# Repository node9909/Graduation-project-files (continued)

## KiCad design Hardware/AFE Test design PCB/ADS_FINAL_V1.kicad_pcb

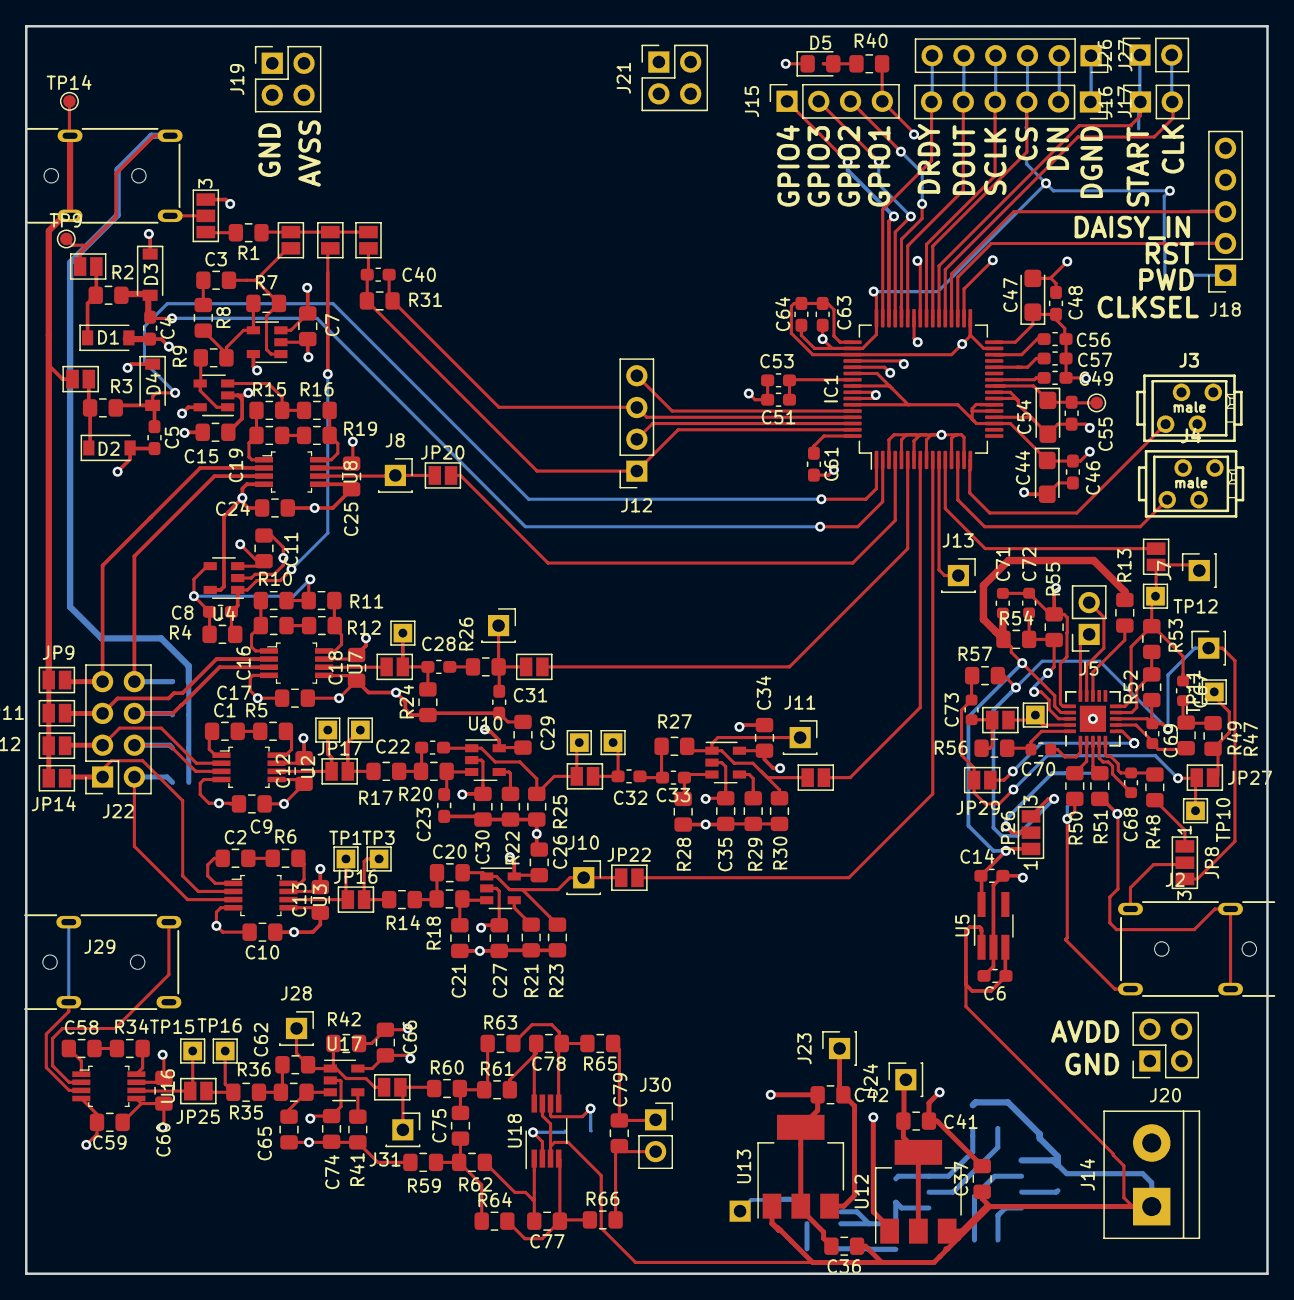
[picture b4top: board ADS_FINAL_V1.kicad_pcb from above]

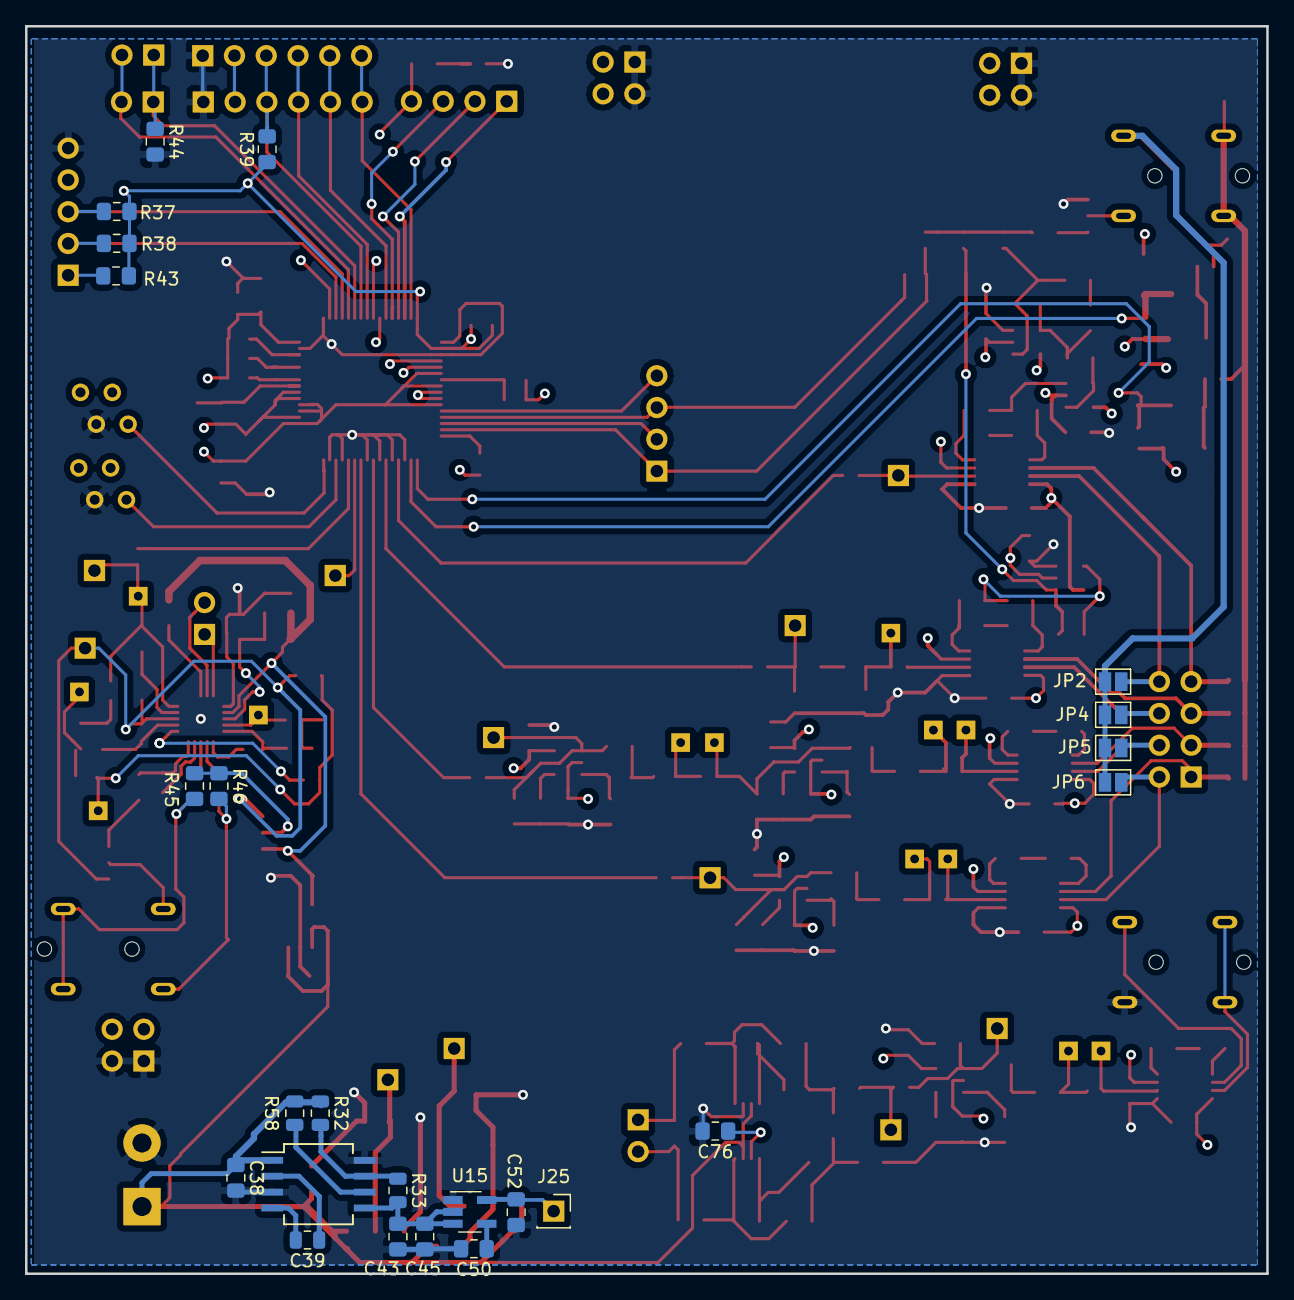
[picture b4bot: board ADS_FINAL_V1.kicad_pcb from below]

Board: 4 copper layers, 99.2 x 99.7 mm, 247 parts (24 on the bottom side), 150 nets.

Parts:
C1, C2, C16, C19, C58: 15u; C_0805_2012Metric_Pad1.15x1.40mm_HandSolder
C3: 1nF; C_0805_2012Metric_Pad1.15x1.40mm_HandSolder
C4, C5: 10pF; C_0603_1608Metric_Pad1.05x0.95mm_HandSolder
C6, C14, C49, C51, C56, C64: 1uF; C_0603_1608Metric_Pad1.05x0.95mm_HandSolder
C7, C9, C10, C11, C12, C13, C15, C17, C18, C24, C25, C26, C27, C29, C30, C34, C35, C59, C60, C66, C74, C75, C76, C77, C78, C79: 100n; C_0805_2012Metric_Pad1.15x1.40mm_HandSolder
C8: 1.5nF; C_0603_1608Metric_Pad1.05x0.95mm_HandSolder
C20, C21, C62, C65: 4.7nF; C_0805_2012Metric_Pad1.15x1.40mm_HandSolder
C22, C23: 4.7nF; C_0603_1608Metric_Pad1.05x0.95mm_HandSolder
C28, C31: 100n; C_0603_1608Metric_Pad1.05x0.95mm_HandSolder
C32, C33: 10nF; C_0603_1608Metric_Pad1.05x0.95mm_HandSolder
C36, C37, C41, C42: 1uF; C_0805_2012Metric_Pad1.15x1.40mm_HandSolder
C38, C43: 4.7uF; C_0805_2012Metric_Pad1.15x1.40mm_HandSolder
C39: 1uF; C_0805_2012Metric
C40: 1M; C_0603_1608Metric_Pad1.05x0.95mm_HandSolder
C44: 10uF; CP_EIA-3216-12_Kemet-S
C45, C52: 2.2uF; C_0805_2012Metric_Pad1.15x1.40mm_HandSolder
C46, C48, C55: 0.1u; C_0603_1608Metric_Pad1.05x0.95mm_HandSolder
C47, C54: 10uF; CP_EIA-3216-10_Kemet-I
C50: 10nF; C_0805_2012Metric_Pad1.15x1.40mm_HandSolder
C53: .1uF; C_0603_1608Metric_Pad1.05x0.95mm_HandSolder
C57: 22uF; C_0603_1608Metric_Pad1.05x0.95mm_HandSolder
C61: 1nF; C_0603_1608Metric_Pad1.05x0.95mm_HandSolder
C63: 0.1uF; C_0603_1608Metric_Pad1.05x0.95mm_HandSolder
C67, C68, C69: 1nF; C_0603_1608Metric
C70, C73: 1000nF; C_0603_1608Metric
C71, C72: 100nF; C_0603_1608Metric
D1, D2, D3, D4: D_Schottky; D_SOD-123
D5: LED; LED_0805_2012Metric_Pad1.15x1.40mm_HandSolder
IC1: ADS1298_By_Oliver; TQFP-64_10x10mm_P0.5mm
J1, J2, J29: AUDIO_JACK_By_OLIVER; MX387GL
J3, J4: external header 2; 0-215464-4_TH_4-pin_male
J5, J16, J26, J30: Conn_01x02; PinSocket_1x02_P2.54mm_Vertical
J6, J7, J8, J9, J10, J11, J13, J23, J24, J25, J28, J31: Conn_01x01; PinSocket_1x01_P2.54mm_Vertical
J12, J15: Conn_01x04; PinSocket_1x04_P2.54mm_Vertical
J14: Screw_Terminal_01x02; TerminalBlock_bornier-2_P5.08mm
J17, J27: DATA_OUT; PinSocket_1x06_P2.54mm_Vertical
J18: Conn_01x05; PinSocket_1x05_P2.54mm_Vertical
J19, J20, J21: Conn_02x02_Counter_Clockwise; PinSocket_2x02_P2.54mm_Vertical
J22: Conn_02x04_Counter_Clockwise; PinSocket_2x04_P2.54mm_Vertical
JP1, JP2, JP4, JP5, JP6, JP7, JP9, JP10, JP11, JP12, JP13, JP14, JP15, JP19: SolderJumper_2_Open; SolderJumper-2_P1.3mm_Open_Pad1.0x1.5mm
JP3, JP8: Jumper_3_Open; SolderJumper-3_P1.3mm_Open_Pad1.0x1.5mm_NumberLabels
JP16, JP17, JP18, JP20, JP21, JP22, JP23, JP24, JP25, JP30: Jumper; SolderJumper-2_P1.3mm_Open_Pad1.0x1.5mm
JP26: SolderJumper_3_Open; SolderJumper-3_P1.3mm_Open_Pad1.0x1.5mm_NumberLabels
JP27, JP28, JP29: Jumper_2_Open; SolderJumper-2_P1.3mm_Open_Pad1.0x1.5mm
M1: AD8232; LFCSP-20-1EP_4x4mm_P0.5mm_EP2.1x2.1mm
R1, R7: 100k; R_0805_2012Metric_Pad1.15x1.40mm_HandSolder
R2, R3: 5k; R_0805_2012Metric_Pad1.15x1.40mm_HandSolder
R4: 1M; R_0805_2012Metric_Pad1.15x1.40mm_HandSolder
R5, R6, R10, R11, R12, R15, R16, R19, R21, R22, R24, R26, R29, R34, R41: 1K; R_0805_2012Metric_Pad1.15x1.40mm_HandSolder
R8, R13, R37, R43, R44: 10k; R_0805_2012Metric_Pad1.15x1.40mm_HandSolder
R9, R38: 10K; R_0805_2012Metric_Pad1.15x1.40mm_HandSolder
R14, R17, R35: 36k; R_0805_2012Metric_Pad1.15x1.40mm_HandSolder
R18, R20, R36, R56, R57, R59, R60, R61, R62, R63, R64, R65, R66: 130k; R_0805_2012Metric_Pad1.15x1.40mm_HandSolder
R23, R42: 9k; R_0805_2012Metric_Pad1.15x1.40mm_HandSolder
R25: 30k; R_0805_2012Metric_Pad1.15x1.40mm_HandSolder
R27: 1.1M; R_0805_2012Metric_Pad1.15x1.40mm_HandSolder
R28: 2.2M; R_0805_2012Metric_Pad1.15x1.40mm_HandSolder
R30: 3K; R_0805_2012Metric_Pad1.15x1.40mm_HandSolder
R31: 1.5nF; R_0805_2012Metric_Pad1.15x1.40mm_HandSolder
R32: 100k; R_0805_2012Metric
R33: 50k; R_0805_2012Metric
R39: 100K; R_0805_2012Metric_Pad1.15x1.40mm_HandSolder
R40, R47, R49, R52, R53: R; R_0805_2012Metric_Pad1.15x1.40mm_HandSolder
R45, R46, R54, R55: 10M; R_0805_2012Metric_Pad1.15x1.40mm_HandSolder
R48: 390k; R_0805_2012Metric_Pad1.15x1.40mm_HandSolder
R50, R51: 180k; R_0805_2012Metric_Pad1.15x1.40mm_HandSolder
R58: 10k; R_0805_2012Metric
TP1, TP2, TP3, TP4, TP5, TP6, TP7, TP10, TP11, TP12, TP13, TP15, TP16: TestPoint; TestPoint_THTPad_1.5x1.5mm_Drill0.7mm
TP8, TP9, TP14: TestPoint; TestPoint_Pad_D1.0mm
U1, U4, U6, U9, U10, U11, U17: OPA333xxDBV; SOT-23-5
U2, U3, U7, U8, U16: INA333AIDGKR; TSSOP-8_W3mm
U5: ADP150; TSOT-23-5_HandSoldering
U12: TLV1117-25; SOT-223-3_TabPin2
U13: MCP1825S; SOT-223-3_TabPin2
U14: MAX889T; SO-8_5.3x6.2mm_P1.27mm
U15: TPS72325; SOT-23-5_HandSoldering
U18: THS4521IDGKT; VSSOP-8_3.0x3.0mm_P0.65mm

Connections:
+5V: C6.1, C36.1, C37.1, C38.1, J14.1, R32.1, R58.1, U5.1, U5.3, U12.3, U13.1, U14.1, U18.3, U18.7
/sheet794AF31F/3V_IN: C14.1, C71.2, JP26.1, M1.17, R13.2, R54.1, U5.5
/sheet794AF31F/EMG_OUT: C67.1, J7.1, JP19.1, M1.10, R53.2, TP12.1
/sheet794AF31F/SDN_MCU: M1.13, R13.1
AD-DC1: J5.2, M1.14
AVDD: C7.1, C11.1, C12.2, C13.2, C15.1, C18.2, C25.2, C26.1, C29.1, C34.1, C41.1, C44.1, C46.1, C60.2, C66.1, D3.1, D4.1, IC1.19, IC1.21, IC1.22, IC1.54, IC1.56, IC1.59, J3.1, J4.1, J20.3, J20.4, J24.1, U1.2, U2.7, U3.7, U4.2, U6.2, U7.7, U8.7, U9.5, U10.5, U11.5, U12.2, U16.7, U17.5
AVSS: C4.2, C5.2, C9.2, C10.2, C17.2, C24.2, C27.1, C30.1, C35.1, C47.1, C48.1, C49.2, C51.2, C52.1, C53.2, C54.2, C55.2, C56.2, C57.2, C59.2, C61.2, C74.1, D1.2, D2.2, IC1.20, IC1.23, IC1.24, IC1.32, IC1.53, IC1.57, IC1.58, J3.3, J4.3, J19.3, J19.4, J25.1, U1.5, U2.4, U3.4, U4.5, U6.5, U7.4, U8.4, U9.2, U10.2, U11.2, U15.5, U16.4, U17.2
CLK: IC1.37, J16.2, J26.2
CLKSEL: IC1.52, J18.1, R43.2
CS: IC1.39, J17.3, J27.3, R39.2
DAISY_CON_1: IC1.41, J18.4
DGND: C6.2, C7.2, C9.1, C10.1, C11.2, C12.1, C13.1, C14.2, C15.2, C17.1, C18.1, C21.1, C23.1, C24.1, C25.1, C26.2, C27.2, C29.2, C30.2, C31.1, C34.2, C35.2, C36.2, C37.2, C38.2, C41.2, C42.2, C43.2, C44.2, C45.2, C46.2, C47.2, C48.2, C50.2, C52.2, C59.1, C60.1, C63.2, C64.2, C65.1, C66.2, C71.1, C72.2, C74.2, C76.2, D5.1, IC1.3, IC1.5, IC1.7, IC1.9, IC1.13, IC1.15, IC1.31, IC1.33, IC1.49, IC1.51, J3.2, J4.2, J14.2, J17.1, J18.5, J19.1, J19.2, J20.1, J20.2, J21.1, J21.2, J27.1, J29.1, JP3.3, M1.16, M1.21, R21.1, R22.1, R23.1, R24.1, R25.1, R28.1, R29.1, R30.1, R41.1, R42.1, R44.2, R55.1, R59.1, U1.3, U2.5, U3.5, U4.3, U5.2, U7.5, U8.5, U12.1, U13.2, U14.3, U14.8, U15.1, U16.5, U18.6
DIN: IC1.34, J17.2, J27.2
DOUT: IC1.43, J17.5, J27.5
DRDY: IC1.47, J17.6, J27.6
DRL3: JP8.1, R48.2
DVDD: C42.1, C63.1, C64.1, IC1.48, IC1.50, J21.3, J21.4, J23.1, R37.1, R38.1, R39.1, R43.1, U13.3
FR1: J5.1, M1.15
GPIO_1: IC1.42, J15.4, R40.1
GPIO_2: IC1.44, J15.3
GPIO_3: IC1.45, J15.2
GPIO_4: IC1.46, J15.1
IN1N: C5.1, D4.2, IC1.1, R3.1
IN1NI: D2.1, JP7.2, R3.2
IN1P: C4.1, D3.2, IC1.2, R2.1
IN1PI: D1.1, JP1.2, R2.2
IN2: IC1.4, JP20.2
IN3: IC1.6, JP21.2
IN4: IC1.8, JP24.2
IN5: IC1.10, JP22.2
IN6: IC1.14, J4.4
IN7: IC1.16, J3.4
IN8: IC1.12, JP19.2
IN+2: J22.8, JP2.2, U8.3
IN+3: J22.6, JP4.2, U7.3
IN+4: J22.4, JP5.2, U2.3
IN+5: J22.2, JP6.2, U3.3
IN+8: J2.2, R45.2, R51.2
IN+9: J29.2, U16.3
IN-2: J22.7, JP9.2, U8.2
IN-3: J22.5, JP11.2, U7.2
IN-4: J22.3, JP12.2, U2.2
IN-5: J22.1, JP14.2, U3.2
IN-8: J2.3, R46.2, R50.2
IN-9: J29.3, U16.2
unnamed: C1.1, U2.1
unnamed: C1.2, R5.2
unnamed: C2.1, U3.1
unnamed: C2.2, R6.2
unnamed: C3.1, R8.1
unnamed: C8.1, R4.2, R10.1, R11.2, U4.4
unnamed: C16.1, R10.2, U7.1
unnamed: C16.2, R12.2
unnamed: C19.1, R15.1, U8.1
unnamed: C19.2, R19.2
unnamed: C20.1, R14.1, R18.2
unnamed: C20.2, J10.1, JP22.1, R23.2, U9.1
unnamed: C21.2, R18.1, U9.3
unnamed: C22.1, R17.1, R20.2
unnamed: C22.2, JP23.1, R25.2, TP6.1, U10.1
unnamed: C23.2, R20.1, U10.3
unnamed: C28.1, R26.1
unnamed: C28.2, JP18.2, R24.2, TP5.1
unnamed: C31.2, J9.1, JP21.1, R26.2
unnamed: C32.1, JP23.2, TP7.1
unnamed: C32.2, C33.2, R27.2
unnamed: C33.1, R28.2, U11.3
unnamed: C39.1, U14.2
unnamed: C39.2, U14.4
unnamed: C43.1, C45.1, R33.2, U14.5, U15.2, U15.3
unnamed: C50.1, U15.4
unnamed: C58.1, U16.1
unnamed: C58.2, R34.2
unnamed: C62.1, R35.1, R36.2
unnamed: C62.2, J28.1, JP30.1, R42.2, U17.1
unnamed: C65.2, R36.1, U17.3
unnamed: C67.2, R47.1, R49.2
unnamed: C68.1, M1.5, R48.1
unnamed: C68.2, M1.4
unnamed: C69.2, M1.7, R49.1
unnamed: C70.1, M1.20, R56.2
unnamed: C70.2, M1.1
unnamed: C72.1, M1.18, R54.2, R55.2
unnamed: C73.1, JP27.2, JP29.1, R57.2, TP10.1
unnamed: C73.2, JP28.2, R56.1
unnamed: C75.1, R59.2, R62.1, R64.1
unnamed: C75.2, R60.2, R61.1, R63.1
unnamed: C76.1, U18.2
unnamed: C77.1, R64.2, R66.1, U18.4
unnamed: C77.2, R62.2, U18.1
unnamed: C78.1, R63.2, R65.2, U18.5
unnamed: C78.2, R61.2, U18.8
unnamed: C79.1, J30.1, R65.1
unnamed: C79.2, J30.2, R66.2
unnamed: D5.2, R40.2
unnamed: J1.1, JP3.2
unnamed: J1.2, JP7.1, JP9.1, JP11.1, JP12.1, JP14.1, TP14.1
unnamed: J1.3, JP1.1, JP2.1, JP4.1, JP5.1, JP6.1, TP9.1
unnamed: J2.1, JP8.2
unnamed: J8.1, JP20.1, U8.6
unnamed: J11.1, JP24.1, R27.1, R30.2, U11.1
unnamed: J31.1, JP30.2, R60.1
unnamed: JP3.1, R1.2
unnamed: JP10.2, JP13.2, JP15.2, R1.1
unnamed: JP16.1, TP1.1, U3.6
unnamed: JP16.2, R14.2, TP3.1
unnamed: JP17.1, TP2.1, U2.6
unnamed: JP17.2, R17.2, TP4.1
unnamed: JP18.1, U7.6
unnamed: JP25.1, TP15.1, U16.6
unnamed: JP25.2, R35.2, TP16.1
unnamed: JP26.2, R45.1, R46.1
unnamed: JP27.1, R47.2, TP11.1
unnamed: JP28.1, M1.19, TP13.1
unnamed: JP29.2, M1.6
unnamed: M1.2, R50.1
unnamed: M1.3, R51.1
unnamed: M1.9, R52.2, R53.1
unnamed: R5.1, U2.8
unnamed: R6.1, U3.8
unnamed: R7.2, R8.2, R9.2, U1.4
unnamed: R9.1, U6.1, U6.4
unnamed: R11.1, R12.1, U7.8
unnamed: R15.2, R16.1, U6.3
unnamed: R16.2, R19.1, U8.8
unnamed: R21.2, U9.4
unnamed: R22.2, U10.4
unnamed: R29.2, U11.4
unnamed: R32.2, R33.1, U14.7
unnamed: R34.1, U16.8
unnamed: R41.2, U17.4
unnamed: R58.2, U14.6
OFFSET_AD8232: IC1.11, J13.1
PWDN: IC1.35, J18.2, R38.2
REF_OUT_AD8232: C69.1, J6.1, JP8.3, JP26.3, M1.8, R52.1, R57.1
RESET: IC1.36, J18.3, R37.2
RLD1: C8.2, JP13.1, R4.1, U4.1
RLD2: C3.2, JP10.1, R7.1, U1.1
RLDIN1: IC1.62, J12.2
RLDINV: C40.2, IC1.61, J12.3, R31.1
RLDOUT1: C40.1, IC1.63, J12.1, JP15.1, R31.2
RLD_REF1: IC1.60, J12.4
SCLK: IC1.40, J17.4, J27.4
START: IC1.38, J16.1, J26.1, R44.1
VCAP1_1: C57.1, IC1.28
VCAP2_1: C56.1, IC1.30
VCAP3_1: C51.1, C53.1, IC1.55
VCAP4_1: C49.1, IC1.26
VREFP1: C54.1, C55.1, IC1.25, TP8.1
WTC_1: C61.1, IC1.64

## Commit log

2019-11-08 Added new files
2019-11-08 update read me
2019-11-10 Report Update
    Added some thing to the report
2019-11-11 update schematic
2019-11-11 Report Update
2019-11-11 updarw
2019-11-18 pc app update
2019-11-20 update report and app
    fixed some buggs in the application
2019-11-20 report update
    added company logo
2019-11-21 add spatial filter
2019-11-24 ùpdate
2020-04-20 added visio files
